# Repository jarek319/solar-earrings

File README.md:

# solar-earrings
A small pair of solar-powered micrcontrollers with onboard RGB LEDs

I was thinking about what could be the smallest possible wearable microcontroller form factor.

Solar powered and other energy harvesting microcontrollers are all the rage, but getting them to stay reliable seems to be difficult. It is helpful to use a current amplifier to monitor junctions in this design.

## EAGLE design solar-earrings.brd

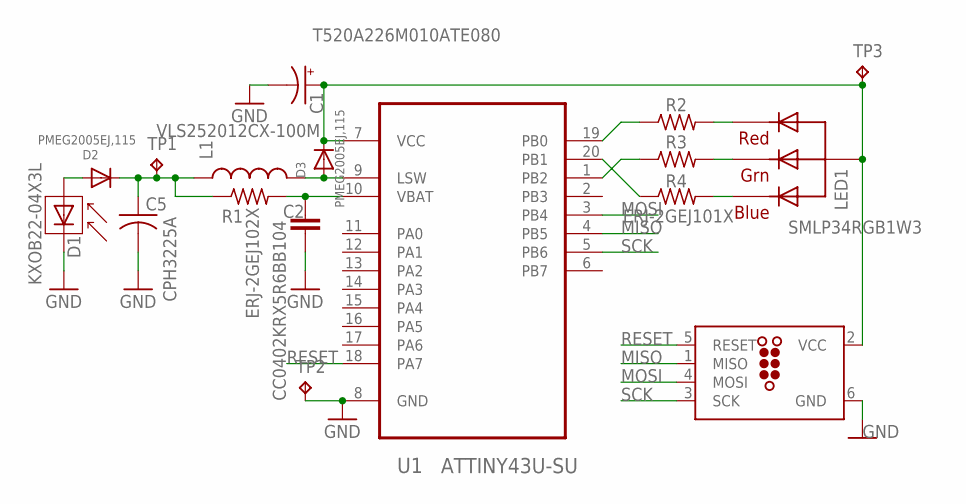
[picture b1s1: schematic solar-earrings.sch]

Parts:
C1: T520A226M010ATE080; EIA3216
C2: CC0402KRX5R6BB104; 0402-CAP
C5: CPH3225A; C3225
D1: KXOB22-04X3L; SOLARBIT-12X1
D2, D3: PMEG2005EJ,115; SOD-323F
J1: TC2030-MCP-NL
L1: VLS252012CX-100M; 1007
LED1: SMLP34RGB1W3; RGB1010
R1: ERJ-2GEJ102X; R0402
R2, R3, R4: ERJ-2GEJ101X; R0402
TP1, TP2, TP3: TPTP06R; TP06R
U1: ATTINY43U-SU; QFN50P400X400X80-21N

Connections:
GND: C1.C (-), C2.2, C5.2, D1.- (C), J1.6 (GND), TP2.TP, U1.8 (GND)
MISO: J1.1 (MISO), U1.4 (PB5)
MOSI: J1.4 (MOSI), U1.3 (PB4)
unnamed: LED1.3 (BLUE), R4.2
unnamed: LED1.4 (GREEN), R3.2
unnamed: LED1.2 (RED), R2.2
unnamed: C1.A (+), D3.C, J1.2 (VCC), LED1.1 (VCC), TP3.TP, U1.7 (VCC)
unnamed: R2.1, U1.19 (PB0)
unnamed: R3.1, U1.1 (PB2)
unnamed: C5.1, D2.C, L1.1, R1.1, TP1.TP
unnamed: R4.1, U1.20 (PB1)
unnamed: D3.A, L1.2, U1.9 (LSW)
unnamed: C2.1, R1.2, U1.10 (VBAT)
unnamed: D1.+ (A), D2.A
RESET: J1.5 (RESET), U1.18 (PA7)
SCK: J1.3 (SCK), U1.5 (PB6)

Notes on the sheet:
SMLP34RGB1W3

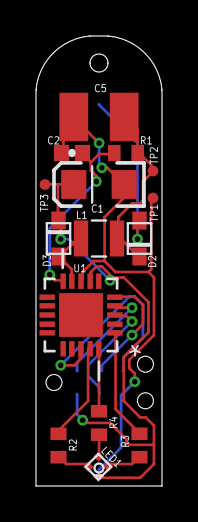
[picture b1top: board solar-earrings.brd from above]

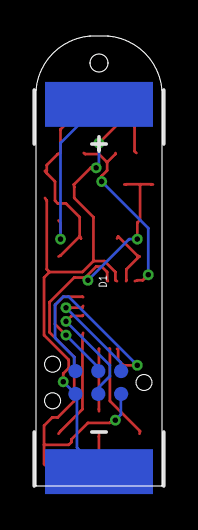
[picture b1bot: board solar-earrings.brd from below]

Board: 2 copper layers, 7.0 x 25.0 mm, 17 parts (2 on the bottom side), 16 nets.

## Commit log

2018-07-05 design tested: erratic performance

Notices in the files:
parts and their libraries:
SparkFun-Sensors: Licensing: CC v3.0 Share-Alike You are welcome to use this library for commercial purposes.
sonik: ©2009 ROFA.cz - modified and updated by Robert Darlington ‹rdarlington@gmail.com›
